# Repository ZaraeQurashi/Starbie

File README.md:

# Starbie 

Starbie is a custom star-shaped PCB that combines electronics, embedded programming, and a virtual pet into one project. Built around the **Seeed Studio XIAO ESP32-C3**, Starbie features a small OLED display, motion sensing, environmental sensors, and interactive buttons that let you care for a digital pet.

##  Features

-  **Custom star-shaped PCB** designed in KiCad
-  **Digital pet** displayed on a 128 × 64 OLED screen
-  **Interactive controls** using two physical buttons
-  **Motion detection** using an MPU6050 accelerometer and gyroscope
-  **Pet-care system** with feeding, playing, petting, and sleeping
-  **Pet statistics** for joy, energy, and fullness
-  **Temperature and humidity readings** using a DHT11 sensor

## Project Overview
Building Starbie meant designing the circuit, laying out and routing a PCB and finally editing the software to control
the hardware. 

I split the project into three main parts:
- Schematic design: Where I took all the components and connected them to each other using Kicad
- PCB Design: Where I turned the schematic into a physical board layout, routed traces and prepared the design
  for manufacturing using KiCad
- Code: Where I edited the program on Arduino and added personal touches to the base program.

### Schematic
The first stage of the project was creating the circuit schematic in KiCad. 

I started by setting up the required footprint and symbol libraries. Then I placed
the components into the schematic and connected them. 

The schematic shows how the XIAO ESP32-C3, OLED display, sensors, buttons, and other components are connected. 

### PCB Layout

Once the schematic was finalized, the next step was to convert it into a physical PCB layout. I imported
all the components into KiCad's PCB Editor and started arranging them on a custom, star shaped board I made
on the edge cuts layer.

After arranging the components, I routed the traces to connect the pads according to the schematic on both the F.CU
and B.CU layer. 

Finally, after the main layout was done, I added game artwork and my initials to the F.Silkscreen layer,
which printed the graphics onto the front of the board.

### Firmware and Digital Pet

For the code and firmware, I started with the existing base code and added a sparkle trail effect to make
the animations more interesting, along with adding my own custom bitmap pet. Then I adjusted the different 
variable values for the pet's health as well as adding the correct connections.

The firmware controls the display, pet interactions, motion sensing, and statistics.

##  Bill of Materials (BOM)

The following table lists the components used to build Starbie, including their suppliers and costs. All prices are in **CAD**.

| Component | Qty. | Supplier | Cost/Item | Total Cost |
|---|---:|---|---:|---:|
| [Seeed Studio Grove OLED Yellow & Blue Display 0.96" (SSD1315) V1.0](https://ca.robotshop.com/products/seeedstudio-grove-oled-yellow-blue-display-096-in-ssd1315-v10) | 1 | RobotShop | $7.86 | $7.86 |
| [6 DOF Gyro, Accelerometer IMU — MPU6050](https://ca.robotshop.com/products/6-dof-gyro-accelerometer-imu-mpu6050?variant=42411369627799) | 1 | RobotShop | $18.43 | $18.43 |
| [Cherry MX2A Red Keyswitch](https://ca.robotshop.com/products/cherry-mx2a-red-keyswitch) | 2 | RobotShop | $2.79 | $5.58 |
| [Seeed Studio XIAO ESP32-C3](https://ca.robotshop.com/products/seeedstudio-xiao-esp32c3-tiny-mcu-w-wi-fi-ble?variant=42740657782935) | 1 | RobotShop | $8.50 | $8.50 |
| [DHT11 Temperature & Humidity Sensor Module Breakout](https://ca.robotshop.com/products/dht11-temperature-humidity-sensor-module-breakout?variant=42412120277143) | 1 | RobotShop | $2.16 | $2.16 |
| [Custom PCB](https://cart.jlcpcb.com/quote?spm=jlcpcb.Public.2006) | 1 | JLCPCB | $15.53 | $15.53 |
| [10 kΩ Resistor](https://ca.robotshop.com/products/sparkfun-resistor-10k-ohm-pth-20-pack) | 1 | RobotShop | $1.36 | $1.36 |
| [Cherry MX Keycap — R2 (Opaque Black)](https://ca.robotshop.com/products/cherry-mx-keycap-r2-opaque-black) | 2 | RobotShop | $1.50 | $3.00 |
| **Estimated shipping** | — | — | — | **$21.97** |
| **Grand Total** | | | | **$84.39** |

**Total estimated cost: $84.39 CAD, including shipping.**

##  Controls

Starbie uses two physical buttons and motion input to interact with the digital pet.

| Input | Action |
|---|---|
| **Button 1** | Opens the radial menu |
| **Tilt the board** | Moves the menu selection |
| **Button 1 while the menu is open** | Confirms the selected action |
| **Button 2** | Toggles the statistics display |
| **Shake the board** | Increases joy by 5, decreases energy by 2, and decreases fullness by 1 |

### Radial Menu

The radial menu contains four actions for caring for the pet.

| Direction | Action | Joy Change | Energy Change | Fullness Change |
|---|---|---:|---:|---:|
| Up | **NAP** | +1 | +18 | -4 |
| Right | **PLAY** | +12 | -9 | -5 |
| Down | **FEED** | +3 | +2 | +18 |
| Left | **PET** | +7 | 0 | 0 |

The values represent the changes applied to the pet's statistics when each action is performed.

##  Hardware Connections

The firmware uses the following pin assignments for the XIAO ESP32-C3.

| Component | Signal | XIAO ESP32-C3 Pin |
|---|---|---|
| OLED display | SDA | D4 / GPIO6 |
| OLED display | SCL | D5 / GPIO7 |
| MPU6050 | SDA | D4 / GPIO6 |
| MPU6050 | SCL | D5 / GPIO7 |
| DHT11 sensor | Data | D1 / GPIO3 |
| Button 1 | Input | D2 / GPIO4 |
| Button 2 | Input | D3 / GPIO5 |

The OLED display uses the I²C address `0x3C`, while the MPU6050 uses the I²C address `0x68`.

##  Firmware

Starbie's firmware is written in **C++ for the Arduino environment**. It manages the display, reads sensor data, handles button input, and updates the digital pet's statistics.

### How It Works

- **Display:** The SSD1306 OLED displays the pet sprite, radial menu, and statistics.
- **Motion sensing:** The MPU6050's accelerometer detects board tilt to navigate the menu and shaking to trigger an interaction.
- **Pet interactions:** Feeding, playing, petting, and sleeping modify the pet's joy, energy, and fullness.
- **Statistics:** The pet's statistics are saved using the ESP32's Preferences functionality, allowing them to persist between restarts.
- **Environmental data:** The DHT11 provides temperature and humidity readings for the statistics display.

The firmware is configured for a **128 × 64 display** and uses a **32 × 32 pixel pet bitmap**.

### Required Libraries

Install the following libraries through the Arduino IDE Library Manager:

- `Adafruit GFX Library`
- `Adafruit SSD1306`
- `Adafruit MPU6050`
- `Adafruit Unified Sensor`
- `DHT sensor library`

The ESP32 board support package must also be installed and configured for the XIAO ESP32-C3.

### Uploading the Firmware

1. Install the Arduino IDE.
2. Install the ESP32 board support package and the libraries listed above.
3. Connect the XIAO ESP32-C3 to your computer.
4. Open the Starbie firmware `.ino` file.
5. Select the appropriate XIAO ESP32-C3 board and serial port.
6. Compile the sketch and resolve any errors.
7. Upload the firmware to the microcontroller.
8. Test the display, buttons, sensors, and pet interactions.

### Manufacturing Files

This repository includes the design files needed to continue editing the PCB.

| File | Purpose |
|---|---|
| `.kicad_sch` | Editable schematic |
| `.kicad_pcb` | Editable PCB layout |
| `.kicad_pro` | KiCad project settings |
| Gerber files | PCB fabrication layers |
| Firmware `.ino` | Arduino firmware |
| `README.md` | Project documentation |

---

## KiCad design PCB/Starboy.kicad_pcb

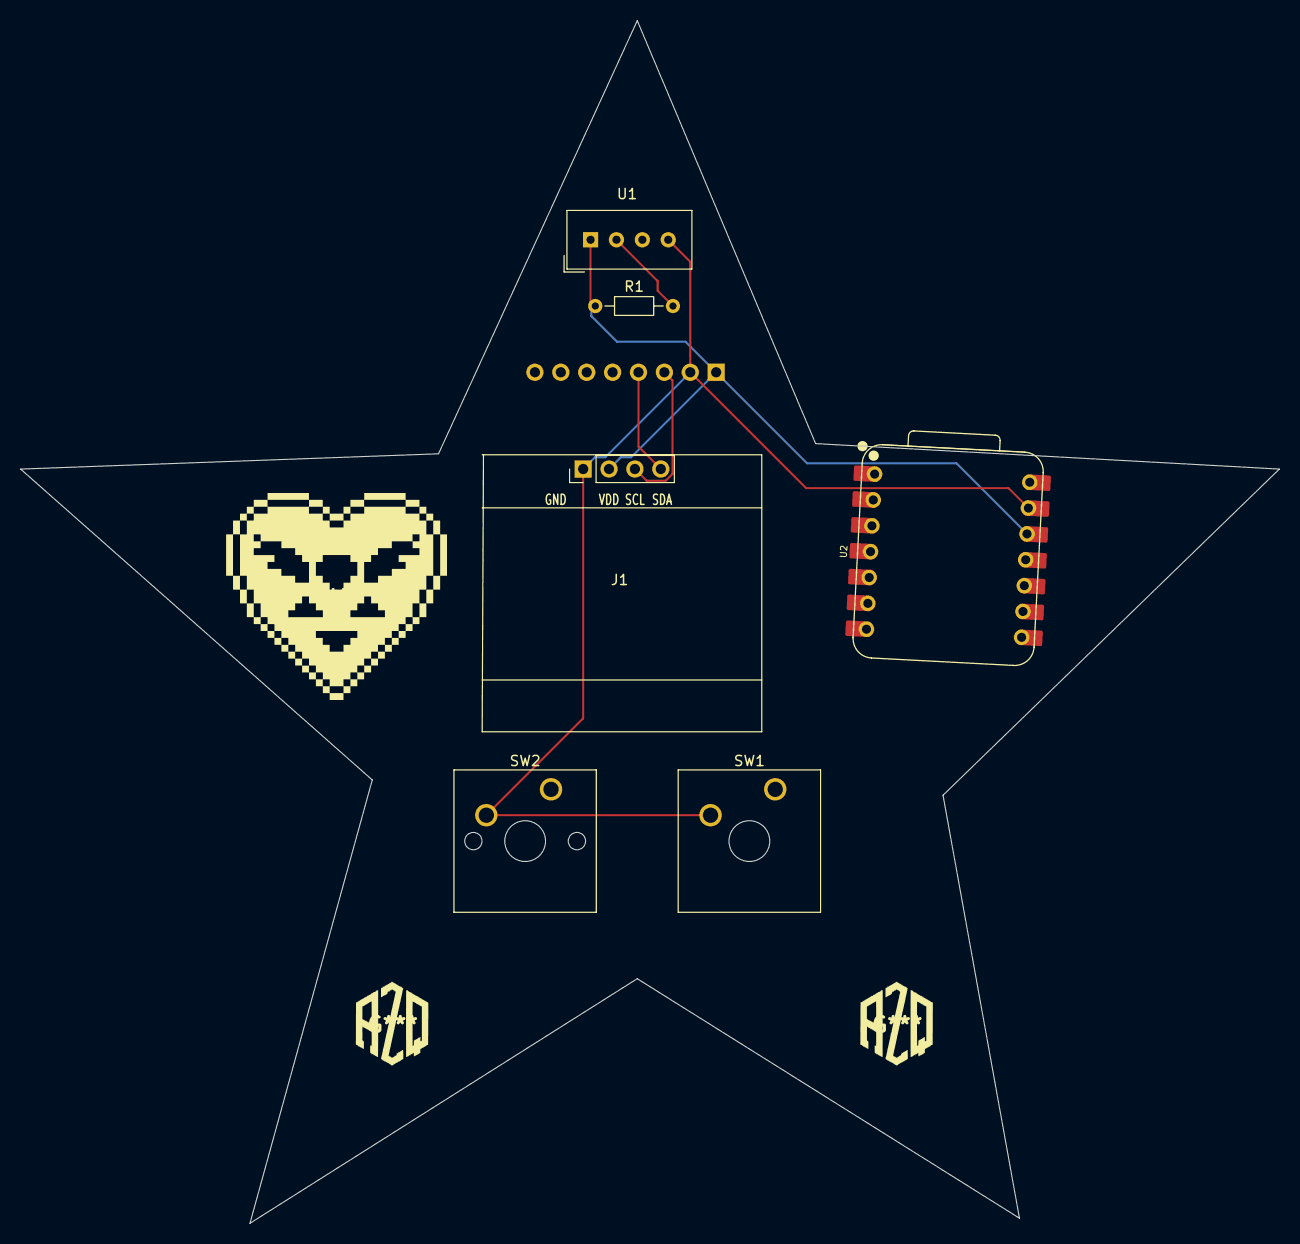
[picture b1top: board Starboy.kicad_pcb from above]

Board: 2 copper layers, 123.5 x 118.0 mm, 7 parts (1 on the bottom side), 5 nets.

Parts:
J1: Conn_01x04_Pin; Display_128x64_096_I2C
J2: Conn_01x08_Pin; PinHeader_1x08_P2.54mm_Vertical
R1: 10K; R_Axial_DIN0204_L3.6mm_D1.6mm_P7.62mm_Horizontal
SW1: SW_Push; SW_Cherry_MX_1.00u_Plate
SW2: SW_Push; SW_Cherry_MX_1.00u_PCB
U1: DHT11; Aosong_DHT11_5.5x12.0_P2.54mm
U2: XIAO-ESP32-C3-SMD; XIAO-ESP32-C6-DIP

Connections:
+3.3V: J1.2, J2.1, R1.1, U1.1 (VDD), U2.12 (3V3_OUT)
/DHT11 DATA: R1.2, U1.2 (DATA)
/SCL: J1.3, J2.3
/SDA: J1.4, J2.4
GND: J1.1, J2.2, SW1.2 (2_2), SW2.2 (2_2), U1.4 (GND), U2.13 (GND)

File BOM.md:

# Starbie – bill of materials

<!-- Generated by Half Life from project cmuvuzkfw01po01os6ryqeq75. Edits here are overwritten on the next sync. -->
<!-- Generated: 2026-10-12T02:25:49.630Z -->

> [!NOTE]
> This parts list is mirrored from [Half Life](https://halflife.hackclub.com). Editing it here will not change the platform's copy, and the next sync overwrites this file.

| Week | Tier | Parts funding |
| --- | --- | --- |
| Week 1 | Tier 1 | $30.00 |

| Part | What it's for | Qty | Unit | Total | Vendor |
| --- | --- | --- | --- | --- | --- |
| [Seeedstudio Grove 4-pin Connector](https://ca.robotshop.com/products/seeedstudio-grove-4-pin-co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 | Conn_01x04_Pin | 1 | $0.90 | $0.90 | [Robot Shop](https://ca.robotshop.com/products/seeedstudio-grove-4-pin-co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 |
| [Conn_01x08_Pin](https://ca.robotshop.com/products/raspberry-pi-pico-headers-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 | Connector | 1 | $1.50 | $1.50 | [Robot Shop](https://ca.robotshop.com/products/raspberry-pi-pico-headers-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 |
| [Mini Push Button Switch Sparkfun Electronnics](https://ca.robotshop.com/products/sfe-mini-push-button-switc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 | SW_Push | 2 | $0.50 | $1.00 | [Robot Shop](https://ca.robotshop.com/products/sfe-mini-push-button-switc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 |
| [XIAO-ESP32-C3-SMD](https://ca.robotshop.com/products/seeedstudio-xiao-esp32c3-t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 | Dev board | 1 | $5.96 | $5.96 | [Robot Shop](https://ca.robotshop.com/products/seeedstudio-xiao-esp32c3-t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 |
| [DHT11](https://ca.robotshop.com/products/dht11-temperature-humidity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 | Humidity/Temperature Sensor | 1 | $1.52 | $1.52 | [Robot Shop](https://ca.robotshop.com/products/dht11-temperature-humidity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 |
| **Parts subtotal** | — | — | — | **$10.88** | — |
| **Tax & shipping** | — | — | — | **$21.05** | — |
| **Total** | — | — | — | **$31.93** | — |

**$1.93 over the tier's funding.** Every tier gives a fixed amount for parts, so this needs cutting back or a higher tier.
